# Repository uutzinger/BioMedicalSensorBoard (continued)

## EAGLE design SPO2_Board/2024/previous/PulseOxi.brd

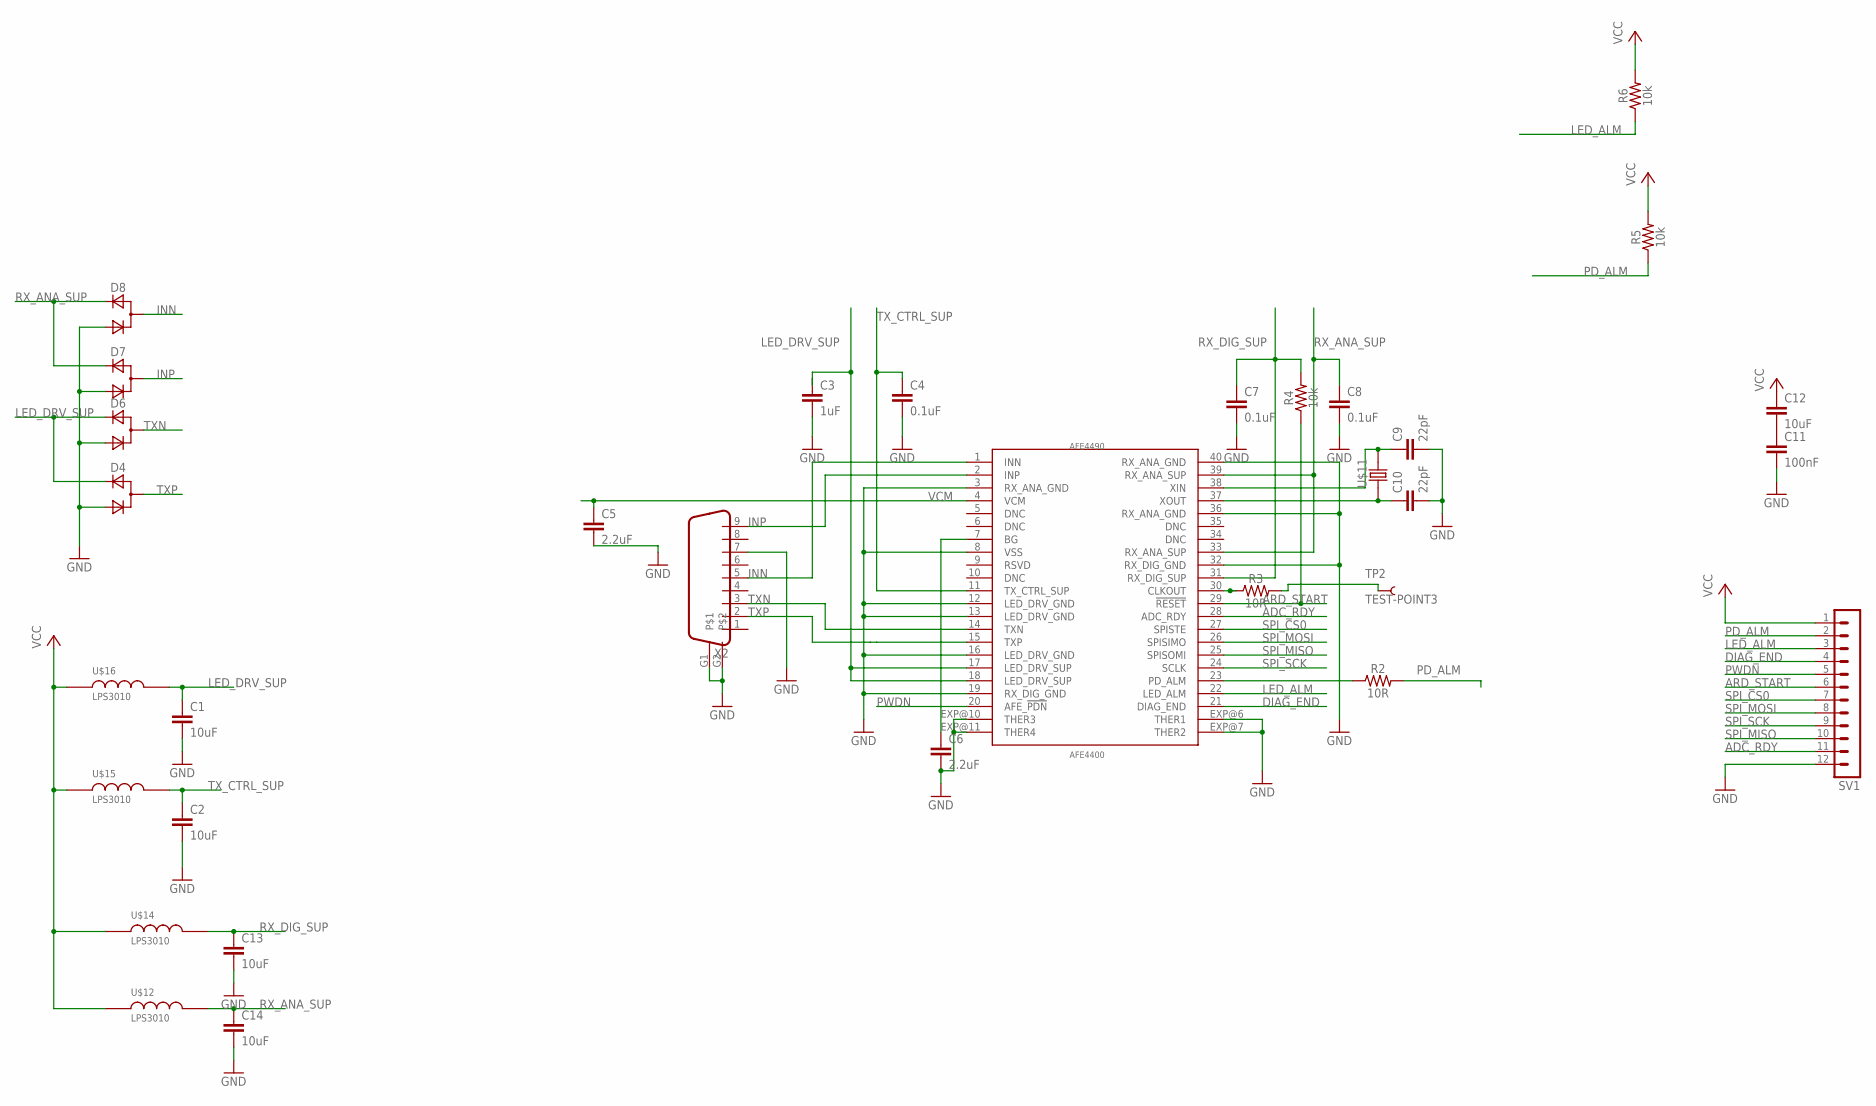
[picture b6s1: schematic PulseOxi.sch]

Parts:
AFE4490: AFE4400; QFN-40
C1, C2, C12, C13, C14: 10uF; 0603
C3: 1uF; 0603
C4, C7, C8: 0.1uF; 0603
C5, C6: 2.2uF; 0603
C9, C10: 22pF; 0603
C11: 100nF; 0603
D4, D6, D7, D8: D_ACACSOT323; SOT323
R2, R3: 10R; 0603
R4, R5, R6: 10k; 0603
SV1: MA12-1
TP2: TEST-POINT3; PAD.03X.03
U$11: ABM3
U$12, U$14, U$15, U$16: LPS3010; LPS
X2: DB9

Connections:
ADC_RDY: AFE4490.28 (ADC_RDY), SV1.11
ARD_START: AFE4490.29 (!RESET), R4.1, SV1.6
DIAG_END: AFE4490.21 (DIAG_END), SV1.4
GND: AFE4490.3 (RX_ANA_GND), AFE4490.8 (VSS), AFE4490.12 (LED_DRV_GND), AFE4490.13 (LED_DRV_GND), AFE4490.16 (LED_DRV_GND), AFE4490.19 (RX_DIG_GND), AFE4490.32 (RX_DIG_GND), AFE4490.36 (RX_ANA_GND), AFE4490.40 (RX_ANA_GND), AFE4490.EXP@6 (THER1), AFE4490.EXP@7 (THER2), AFE4490.EXP@10 (THER3), AFE4490.EXP@11 (THER4), C1.2, C2.2, C3.2, C4.2, C5.2, C6.2, C7.2, C8.2, C9.2, C10.2, C11.2, C13.2, C14.2, D4.2 (C), D6.2 (C), D7.2 (C), D8.2 (C), SV1.12, X2.7, X2.G1, X2.G2
INN: AFE4490.1 (INN), D8.1 (CA), X2.5
INP: AFE4490.2 (INP), D7.1 (CA), X2.9
LED_ALM: AFE4490.22 (LED_ALM), R6.1, SV1.3
LED_DRV_SUP: AFE4490.17 (LED_DRV_SUP), AFE4490.18 (LED_DRV_SUP), C1.1, C3.1, D4.3 (A), D6.3 (A), U$16.2
unnamed: C11.1, C12.2
unnamed: AFE4490.30 (CLKOUT), R3.1
unnamed: R3.2, TP2.P$1
unnamed: AFE4490.23 (PD_ALM), R2.1
unnamed: AFE4490.38 (XIN), C9.1, U$11.2
unnamed: AFE4490.37 (XOUT), C10.1, U$11.1
unnamed: AFE4490.7 (BG), C6.1
PD_ALM: R2.2, R5.1, SV1.2
PWDN: AFE4490.20 (AFE_!PDN), SV1.5
RX_ANA_SUP: AFE4490.33 (RX_ANA_SUP), AFE4490.39 (RX_ANA_SUP), C8.1, C14.1, D7.3 (A), D8.3 (A), U$12.2
RX_DIG_SUP: AFE4490.31 (RX_DIG_SUP), C7.1, C13.1, R4.2, U$14.2
SPI_CS0: AFE4490.27 (SPISTE), SV1.7
SPI_MISO: AFE4490.25 (SPISOMI), SV1.10
SPI_MOSI: AFE4490.26 (SPISIMO), SV1.8
SPI_SCK: AFE4490.24 (SCLK), SV1.9
TXN: AFE4490.14 (TXN), D6.1 (CA), X2.3
TXP: AFE4490.15 (TXP), D4.1 (CA), X2.2
TX_CTRL_SUP: AFE4490.11 (TX_CTRL_SUP), C2.1, C4.1, U$15.2
VCC: C12.1, R5.2, R6.2, SV1.1, U$12.1, U$14.1, U$15.1, U$16.1
VCM: AFE4490.4 (VCM), C5.1

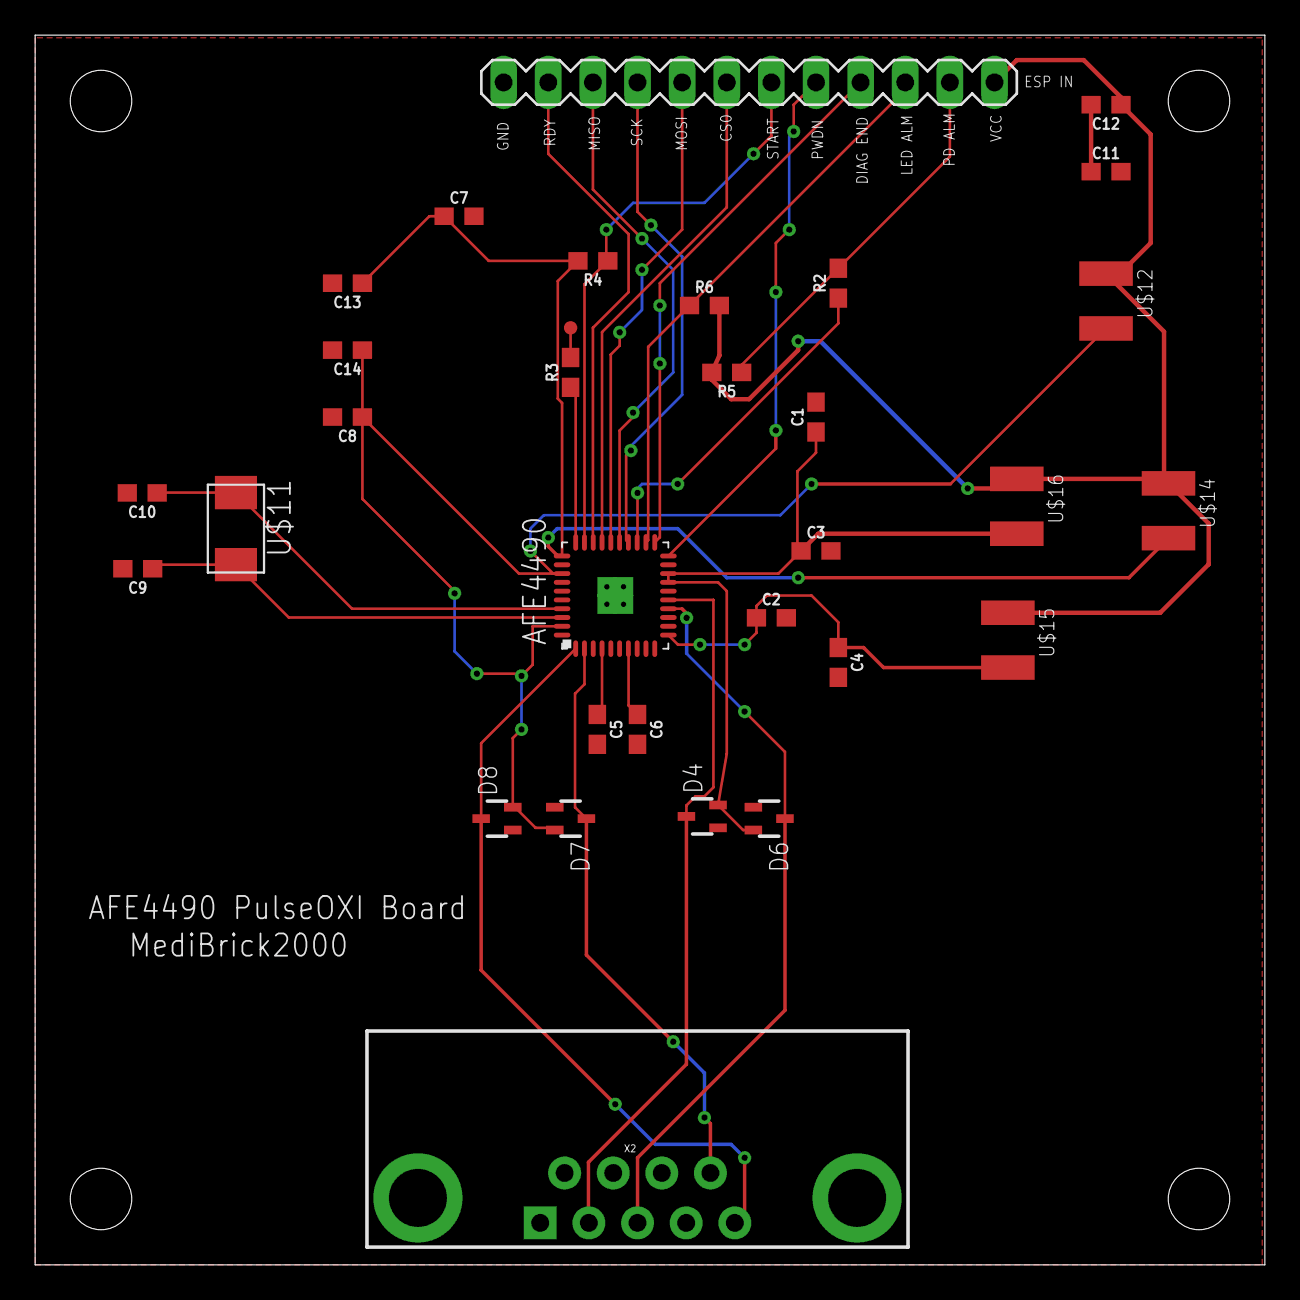
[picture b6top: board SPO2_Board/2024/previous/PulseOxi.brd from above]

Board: 2 copper layers, 70.0 x 70.0 mm, 32 parts (0 on the bottom side), 28 nets.
